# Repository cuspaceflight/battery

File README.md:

# 2S Li-Ion Battery Charger and Balancer

This is a small pcb intended to test the new parts used to charge and balance
the 2S 18650 battery pack onboard Martlet IV.

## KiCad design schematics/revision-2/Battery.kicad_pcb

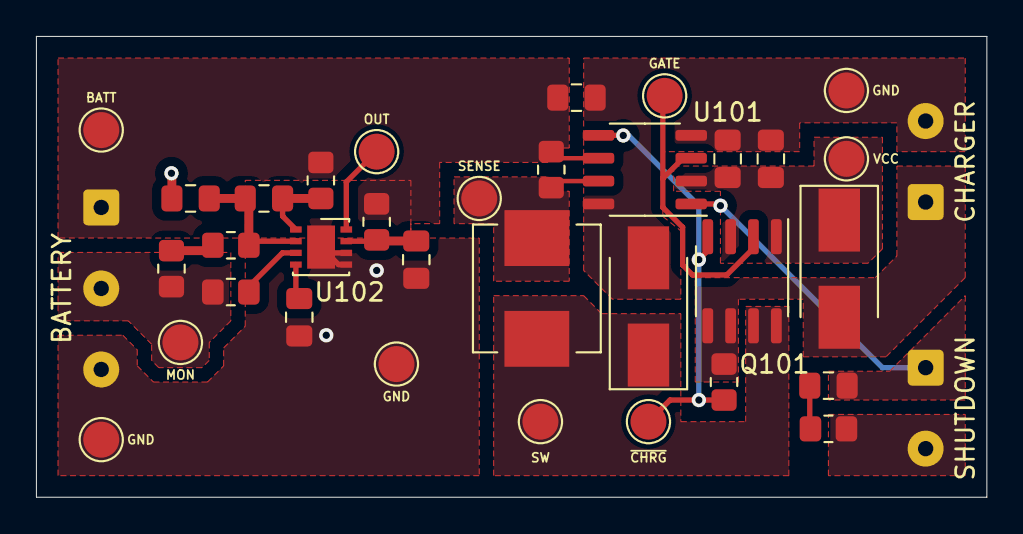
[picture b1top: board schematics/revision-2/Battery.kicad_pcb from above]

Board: 2 copper layers, 52.8 x 25.6 mm, 35 parts (0 on the bottom side), 18 nets.

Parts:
BATT: TestPoint; TestPoint_Pad_D2.0mm
BATTERY: BATTERY; SolderWire-0.25sqmm_1x03_P4.5mm_D0.65mm_OD2mm
C101, C103, C104, C105: 100n; C_0805_2012Metric_Pad1.18x1.45mm_HandSolder
C102: 10u; C_0805_2012Metric_Pad1.18x1.45mm_HandSolder
C106: 470n; C_0805_2012Metric_Pad1.18x1.45mm_HandSolder
C107: 22u; C_0805_2012Metric_Pad1.18x1.45mm_HandSolder
C108: 330n; C_0805_2012Metric_Pad1.18x1.45mm_HandSolder
CHARGER: CHG; SolderWire-0.25sqmm_1x02_P4.5mm_D0.65mm_OD2mm
D101, D102: B330; D_SMB_Handsoldering
GATE: TestPoint; TestPoint_Pad_D2.0mm
GND: TestPoint; TestPoint_Pad_D2.0mm
GND#2, GND#3: TestPoint; TestPoint_Pad_D2.0mm
L101: 6u8; L_Wuerth_HCI-7050
MON: TestPoint; TestPoint_Pad_D2.0mm
OUT: TestPoint; TestPoint_Pad_D2.0mm
Q101: Si9933CDY; SOIC-8_3.9x4.9mm_P1.27mm
R101: 100k; R_0805_2012Metric_Pad1.20x1.40mm_HandSolder
R102, R105, R107: 100; R_0805_2012Metric_Pad1.20x1.40mm_HandSolder
R103: 50m; R_0805_2012Metric_Pad1.20x1.40mm_HandSolder
R104, R106: 160; R_0805_2012Metric_Pad1.20x1.40mm_HandSolder
R108: 2k2; R_0805_2012Metric_Pad1.20x1.40mm_HandSolder
SENSE: TestPoint; TestPoint_Pad_D2.0mm
SHUTDOWN: SDN; SolderWire-0.25sqmm_1x02_P4.5mm_D0.65mm_OD2mm
SW: TestPoint; TestPoint_Pad_D2.0mm
U101: LTC4002ES8; SO-8_3.9x4.9mm_P1.27mm
U102: BQ29200; BQ2920X
VCC: TestPoint; TestPoint_Pad_D2.0mm

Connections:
/BATT_MON: BATTERY.2, MON.1, R106.1, R107.1
/COMP: C106.1, SHUTDOWN.1, U101.1 (COMP)
/SENSE: L101.2, R103.2, SENSE.1, U101.7 (SENSE)
/VCC_CHG: C101.1, C102.1, D101.1, Q101.1 (S1), Q101.3 (S2), U101.2 (VCC), VCC.1
/V_SW: D102.1, L101.1, Q101.7 (D1), Q101.8 (D1), SW.1
/~CHRG: Q101.4 (G2), R101.1, U101.5 (~CHRG)
GND: BATTERY.3, C101.2, C102.2, C104.2, C105.2, C107.2, C108.2, CHARGER.2, D102.2, GND.1, GND#2.1, GND#3.1, R108.2, SHUTDOWN.2, U101.4 (GND), U101.8 (NTC), U102.5 (GND), U102.6 (~CB_EN), U102.9 (PGND)
unnamed: C103.1, R104.2, U102.1 (VC2)
unnamed: C103.2, C105.1, R105.2, U102.2 (VC1)
unnamed: C104.1, R102.2, U102.7 (VDD)
unnamed: C106.2, R108.1
unnamed: C108.1, U102.4 (CD)
unnamed: CHARGER.1, D101.2, Q101.5 (D2), Q101.6 (D2), R101.2
unnamed: GATE.1, Q101.2 (G1), U101.3 (GATE)
unnamed: R105.1, R106.2
unnamed: R107.2, U102.3 (VC1_CB)
unnamed: OUT.1, U102.8 (OUT)
VBATT: BATT.1, BATTERY.1, C107.1, R102.1, R103.1, R104.1, U101.6 (BAT)

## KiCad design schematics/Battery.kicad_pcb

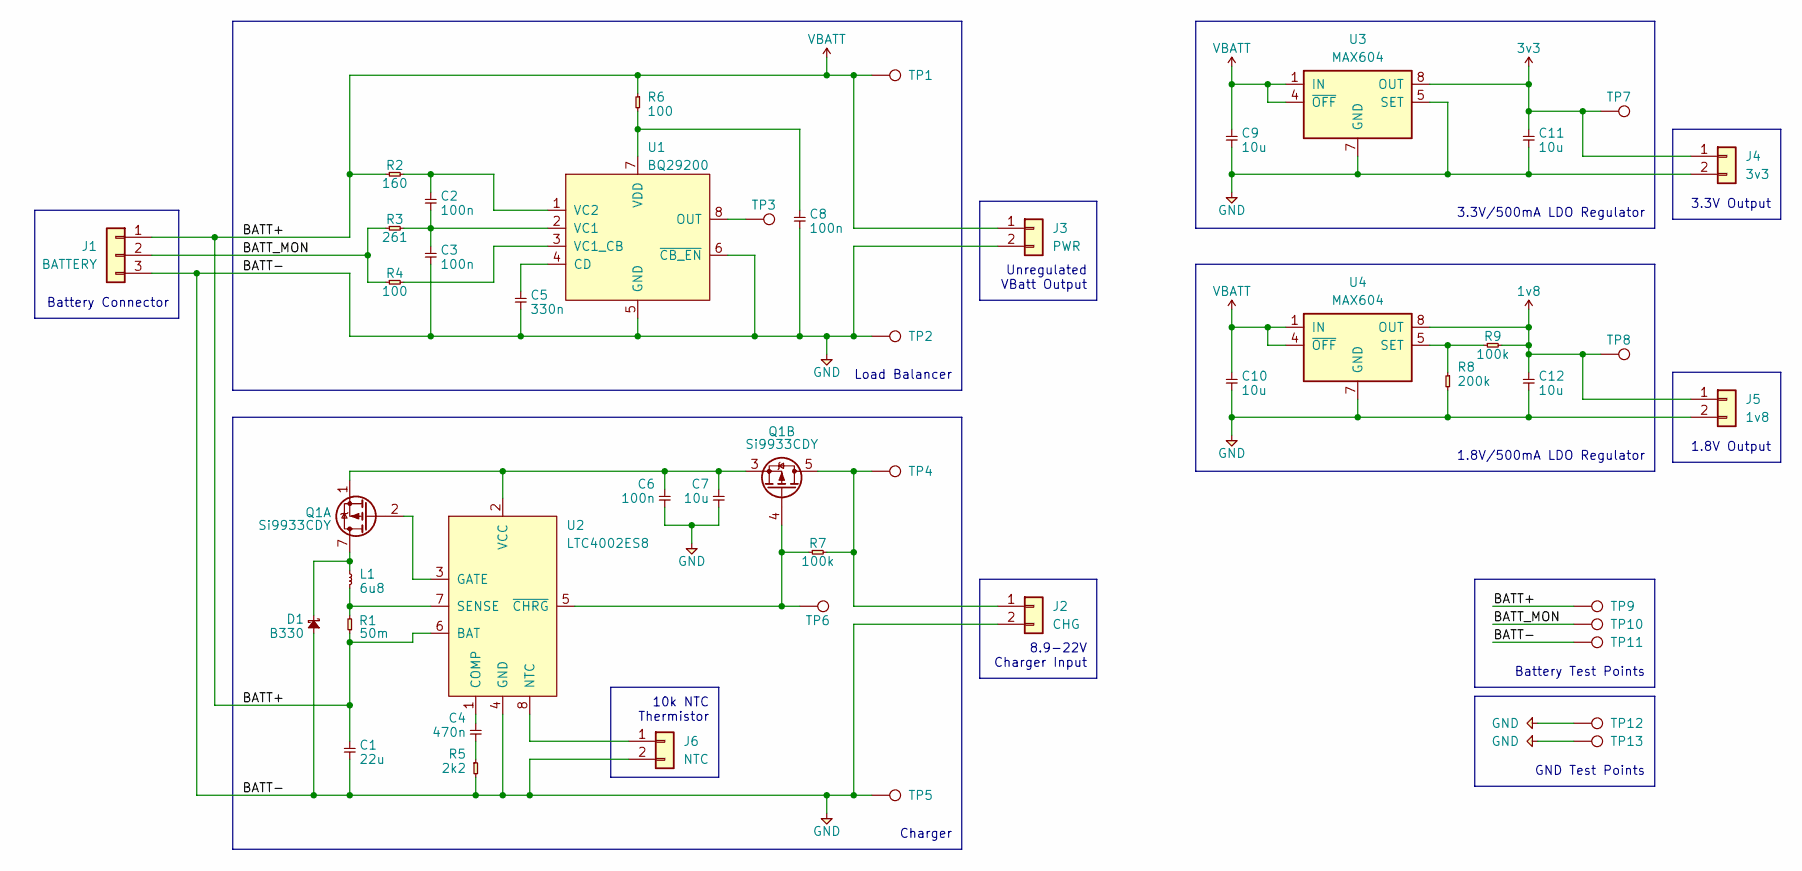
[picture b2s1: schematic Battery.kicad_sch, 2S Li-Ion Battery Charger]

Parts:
C1: 22u; C_0805_2012Metric_Pad1.18x1.45mm_HandSolder; Farnell 2525135
C2, C3, C6, C8: 100n; C_0805_2012Metric_Pad1.18x1.45mm_HandSolder; Farnell 1759166
C4: 470n; C_0805_2012Metric_Pad1.18x1.45mm_HandSolder; Farnell 2320847
C5: 330n; C_0805_2012Metric_Pad1.18x1.45mm_HandSolder; Farnell 2346946
C7, C9, C10, C11, C12: 10u; C_0805_2012Metric_Pad1.18x1.45mm_HandSolder; Farnell 2611940
D1: B330; D_SMB_Handsoldering
J1: BATTERY; Molex_Nano-Fit_105313-xx03_1x03_P2.50mm_Horizontal; Farnell 2820685
J2: CHG; Molex_Nano-Fit_105313-xx02_1x02_P2.50mm_Horizontal; Farnell 2576866
J3: PWR; Molex_Nano-Fit_105313-xx02_1x02_P2.50mm_Horizontal; Farnell 2576866
J4: 3v3; Molex_Nano-Fit_105313-xx02_1x02_P2.50mm_Horizontal; Farnell 2576866
J5: 1v8; Molex_Nano-Fit_105313-xx02_1x02_P2.50mm_Horizontal; Farnell 2576866
J6: NTC; Molex_Nano-Fit_105313-xx02_1x02_P2.50mm_Horizontal; Farnell 2576866
L1: 6u8; L_Wuerth_HCI-7050
Q1: Si9933CDY; SOIC-8_3.9x4.9mm_P1.27mm; Farnell 1779275
R1: 50m; R_0805_2012Metric_Pad1.20x1.40mm_HandSolder; Farnell 2008296
R2: 160; R_0805_2012Metric_Pad1.20x1.40mm_HandSolder; Farnell 2694996
R3: 261; R_0805_2012Metric_Pad1.20x1.40mm_HandSolder; Farnell 2303485
R4, R6: 100; R_0805_2012Metric_Pad1.20x1.40mm_HandSolder; Farnell 2447552
R5: 2k2; R_0805_2012Metric_Pad1.20x1.40mm_HandSolder; Farnell 1576464
R7, R9: 100k; R_0805_2012Metric_Pad1.20x1.40mm_HandSolder; Farnell 2380290
R8: 200k; R_0805_2012Metric_Pad1.20x1.40mm_HandSolder; Farnell 2380505
TP1, TP2, TP3, TP4, TP5, TP6, TP7, TP8, TP9, TP10, TP11, TP12, TP13: TestPoint; TestPoint_Pad_D2.0mm
U1: BQ29200; BQ2920X; Farnell 2383074
U2: LTC4002ES8; SO-8_3.9x4.9mm_P1.27mm
U3, U4: MAX604; SOIC-8_3.9x4.9mm_P1.27mm; Farnell 2518575

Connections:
1v8: C12.1, J5.1, R9.2, TP8.1, U4.8 (OUT)
3v3: C11.1, J4.1, TP7.1, U3.8 (OUT)
/BATT_MON: J1.2, R3.1, R4.1, TP10.1
GND: C1.2, C3.2, C5.2, C6.2, C7.2, C8.2, C9.2, C10.2, C11.2, C12.2, D1.2, J1.3, J2.2, J3.2, J4.2, J5.2, J6.2, R5.2, R8.2, TP2.1, TP5.1, TP11.1, TP12.1, TP13.1, U1.5 (GND), U1.6 (~CB_EN), U2.4 (GND), U3.2 (GND), U3.3 (GND), U3.5 (SET), U3.6 (GND), U3.7 (GND), U4.2 (GND), U4.3 (GND), U4.6 (GND), U4.7 (GND)
unnamed: C2.1, R2.2, U1.1 (VC2)
unnamed: C2.2, C3.1, R3.2, U1.2 (VC1)
unnamed: C4.1, U2.1 (COMP)
unnamed: C4.2, R5.1
unnamed: C5.1, U1.4 (CD)
unnamed: C6.1, C7.1, Q1.1 (S1), Q1.3 (S2), U2.2 (VCC)
unnamed: C8.1, R6.2, U1.7 (VDD)
unnamed: D1.1, L1.1, Q1.7 (D1), Q1.8 (D1)
unnamed: J2.1, Q1.5 (D2), Q1.6 (D2), R7.2, TP4.1
unnamed: J6.1, U2.8 (NTC)
unnamed: L1.2, R1.2, U2.7 (SENSE)
unnamed: Q1.2 (G1), U2.3 (GATE)
unnamed: Q1.4 (G2), R7.1, TP6.1, U2.5 (~CHRG)
unnamed: R4.2, U1.3 (VC1_CB)
unnamed: R8.1, R9.1, U4.5 (SET)
unnamed: TP3.1, U1.8 (OUT)
VBATT: C1.1, C9.1, C10.1, J1.1, J3.1, R1.1, R2.1, R6.1, TP1.1, TP9.1, U2.6 (BAT), U3.1 (IN), U3.4 (~OFF), U4.1 (IN), U4.4 (~OFF)

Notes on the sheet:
GND Test Points
1.8V/500mA LDO Regulator
1.8V Output
8.9-22V Charger Input
Load Balancer
Battery Test Points
3.3V Output
Unregulated VBatt Output
3.3V/500mA LDO Regulator
Charger
10k NTC Thermistor
Battery Connector

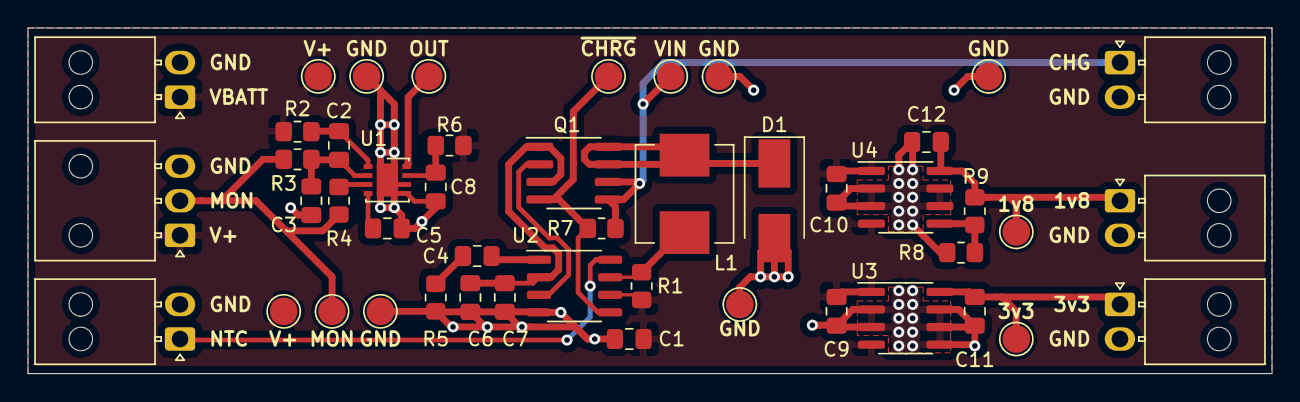
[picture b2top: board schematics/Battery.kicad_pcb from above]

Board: 2 copper layers, 90.0 x 25.0 mm, 47 parts (0 on the bottom side), 21 nets.

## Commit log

2021-10-16 Redraw board and plot Gerbers
2021-10-17 Add back silkscreen text
2021-10-18 Fix sense resistor and resize board
2021-10-21 Reorganise files and expose copper under LDOs
2021-10-21 Add README
2021-12-05 Remove plot files (moved to Google Drive)
2021-12-13 Update to KiCad 6
2021-12-13 Create revision 2 schematic
2021-12-27 Fixes
2022-01-26 Finish revision 2
